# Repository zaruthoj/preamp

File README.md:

# preamp
INA217 based preamp board.

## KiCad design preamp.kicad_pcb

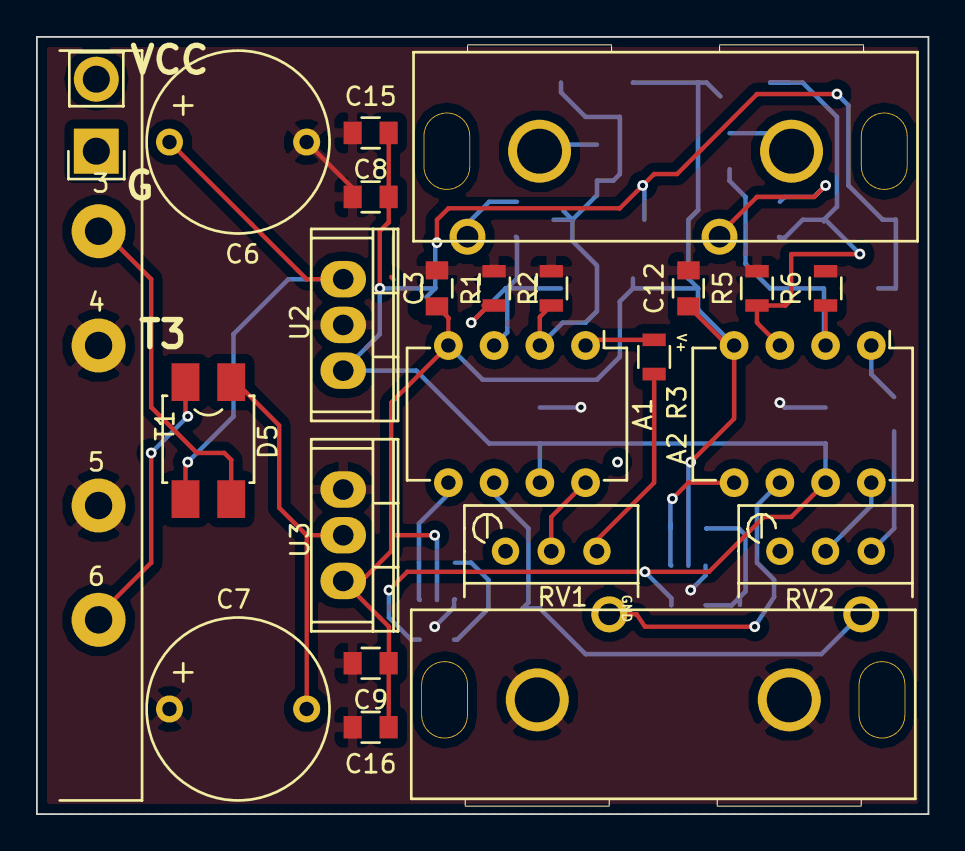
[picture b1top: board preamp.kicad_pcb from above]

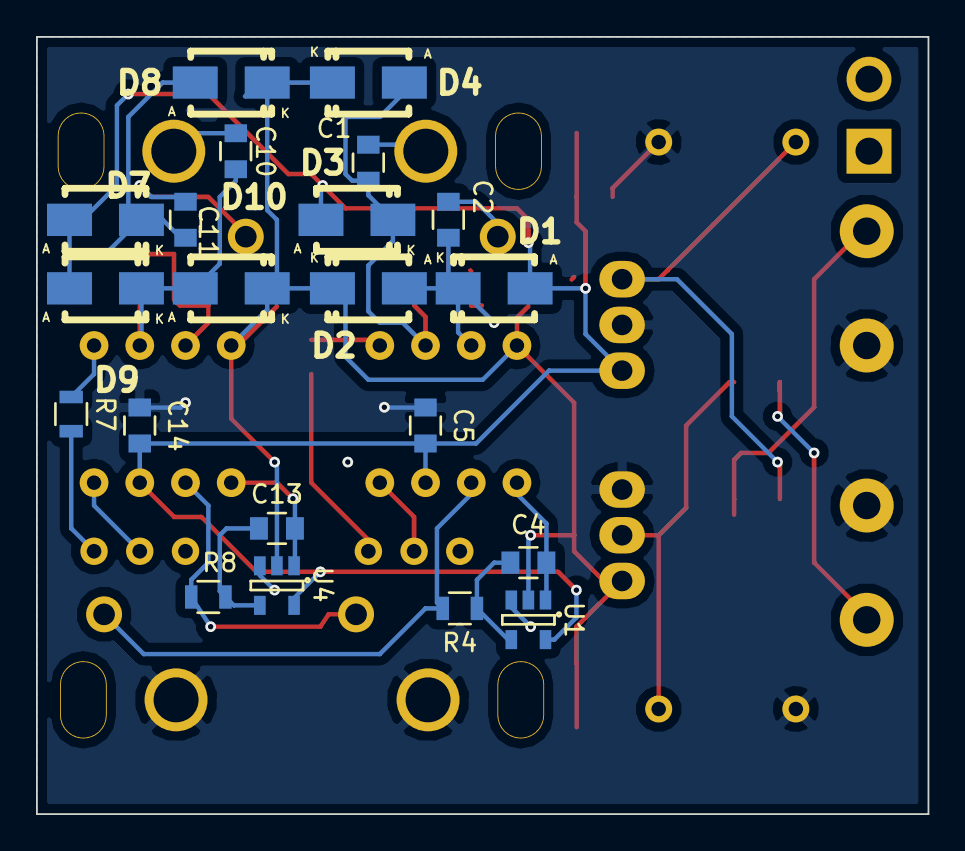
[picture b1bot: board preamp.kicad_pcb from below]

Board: 2 copper layers, 49.5 x 43.2 mm, 45 parts (21 on the bottom side), 27 nets.

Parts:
A1, A2: INA217; DIP-8_W7.62mm
C1, C2, C10, C11: 1uf; C_0805
C3, C4, C5, C12, C13, C14: 0.1uf; C_0805
C6, C7: 1000uF; preamp_Elko_vert_20x10mm_RM7.5
C8: 0.1uF; C_0805
C9: 1uf t; C_0805
C15: .1uf; C_0805
C16: C_0805
D1, D2, D3, D4, D7, D8, D9, D10: D; Diode-SMA_Standard_RevA_26July2010
D5: Diode_Bridge; Bridge-Rectifier-SOIC-4
P1, P3: CONN_01X04; preamp_RCA_STEREO
P2: CONN_01X02; Power_Pin_Header
R1, R2, R5, R6: 2.2k; R_0805
R3, R7: 1k; R_0805
R4, R8: 1M; R_0805
RV1, RV2: 10k; Potentiometer_Bourns_3296W_3-8Zoll_Inline_ScrewUp
T1: TRANSFO2; preamp_transformer_6pin_half
U1, U4: OPA137N; SOT-23-5
U2: LM7815CT; TO-220
U3: LM7915CT; TO-220

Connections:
+15V: A1.7, A2.7, C5.2, C8.1, C14.2, C15.1, D1.1, D3.1, D7.1, D9.1, U1.5, U2.3, U4.5
-15V: A1.4, A2.4, C3.2, C9.2, C12.2, C16.2, D2.2, D4.2, D8.2, D10.2, U1.2, U3.3, U4.2
GND: C3.1, C5.1, C6.2, C7.1, C8.2, C9.1, C12.1, C14.1, C15.2, C16.1, P3.1, P3.3, R1.2, R2.2, R5.2, R6.2, T1.4, T1.5, U1.3, U2.2, U3.1, U4.3
unnamed: A1.1, R3.2
unnamed: A1.2, C1.1, D3.2, D4.1, R2.1
unnamed: A1.3, C2.1, D1.2, D2.1, R1.1
unnamed: A1.5, C4.2, U1.1
unnamed: A1.6, P3.4, R4.1
unnamed: A1.8, RV1.2
unnamed: A2.1, R7.2
unnamed: A2.2, C10.1, D9.2, D10.1, R6.1
unnamed: A2.3, C11.1, D7.2, D8.1, R5.1
unnamed: A2.5, C13.2, U4.1
unnamed: A2.6, P3.2, R8.1
unnamed: A2.8, RV2.2
unnamed: C1.2, P1.3
unnamed: C2.2, P1.4
unnamed: C4.1, R4.2, U1.4
unnamed: C6.1, D5.3, U2.1
unnamed: C7.2, D5.1, U3.2
unnamed: C10.2, P1.1
unnamed: C11.2, P1.2
unnamed: C13.1, R8.2, U4.4
unnamed: D5.2, T1.6
unnamed: D5.4, T1.3
unnamed: R3.1, RV1.3
unnamed: R7.1, RV2.3

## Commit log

2015-06-08 Initial project files
2015-06-09 First rev complete.
2015-06-09 Add silkscreen labels for IO
2015-06-12 Add PSU and additional channel to schematic and parts
2015-06-16 Expand to stereo, add AC power supply. Not done yet.
2015-06-16 More work on stereo plus PCB footprint
2015-06-16 More footprint improvements.
2015-06-16 Finish adding PSU and second channel. Ready for fab?
2015-06-16 Gerber files for PSU stereo
2015-06-16 Cleanup a label I missed
2015-06-17 Add power cable items to BOM and misc layout cleanup.
2015-06-17 Clean up a couple of stray traces.
2015-06-21 Fix transformer value to adjust for RMS vs peak to peak voltage. Add extra filtering caps at PSU output. Fix the diode bridge pads.
2015-06-21 Missed a file on previous commit
2015-06-21 Fix trim pot values to allow for min gain of 1.1x. Also generate gerbers.
2015-06-21 Final ordered version on Oshpark.
